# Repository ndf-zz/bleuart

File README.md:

# bleuart

ESP32 BLE to RS232 bridge

	BLE  <->  UART  <-- RX (RS232)
	                --> TX (RS232)

Using an ESP32-WROOM-32E module, BLEUART provides
a low-tech BLE to RS232 UART bridge. Data is transferred
via write and notify under a single custom GATT service
with ID 11e6b0a4-99c7-4647-956b-8a57cb5907d9.

Advertises device "location" (CNAME) via
manufacturer data. Initial bonding PIN is 0.

## Characteristics

UUID | Function | Type | Actions
--- | --- | --- | ---
0000b0a4-99c7-4647-956b-8a57cb5907d9 | Pin | uint32 (0-999999) | write
0001b0a4-99c7-4647-956b-8a57cb5907d9 | UART RX | bytes | notify
0010b0a4-99c7-4647-956b-8a57cb5907d9 | UART TX | bytes | write
0100b0a4-99c7-4647-956b-8a57cb5907d9 | CNAME "Location" | bytes | read/write
1000b0a4-99c7-4647-956b-8a57cb5907d9 | DNAME "Device Name" | bytes | write
f074b0a4-99c7-4647-956b-8a57cb5907d9 | FOTA | bytes | write
0x2a26 | Firmware Version | bytes | read

## Known Issues/Limitations

   - Secure boot V1 is used only as a fancy CRC for OTA updates.
     Todo: Move to V2.
   - Re-flashable bootloader needs to be booted once and then re-flashed
     to correct the re-flashable stage 2 digest. Todo: Move to V2 and or
     one-time flash.
   - LE security is circumvented through use of fixed pairing pin. Todo: OOB.
   - Private addrs do not yet work as expected. Todo: Investigate 
     implementation of RPA 0x2ac9.
   - RS232 line driver/receiver is always on, even when device cannot
     receive data due to light sleep. Todo: Use GPIO
     to switch power to line driver.
   - Test pads GPIO13/15 are inaccessible and floating. Todo:
     Add pull-ups and relocate pads with nearby ground pad for
     factory reset option.
   - Reflashable plain text bootloader assumed. Todo: Investigate
     encrypted flash, encrypted OTA transport.
   - App rollback not supported. Todo: Debug OTA partition
     errors in bootloader and check ota rollback tools.

## FOTA

Write SSID and PSK to GATT characteristic 0xf074 separated
by a null character. Eg:

	b'SSID\0wpapskstr'

Device will connect to nominated ssid, fetch firmware 
then reboot. Base URL for update is set in menuconfig
options. In case of error or timeout, device will reboot to
previous firmware.

Update file requested:

	11e6b0a4-99c7-4647-956b-8a57cb5907d9.bin

## Build & Flash

   - Install ESP-IDF & run export
   - Set target
   - Create secure boot signing key if required
   - Run burnin.sh, reboot board and then run reburn.sh

	$ . ../esp-idf/export.sh
	$ idf.py set-target esp32
	$ idf.py secure-generate-signing-key secure_boot_signing_key.pem
	$ ./burnin.sh
	$ ./reburn.sh

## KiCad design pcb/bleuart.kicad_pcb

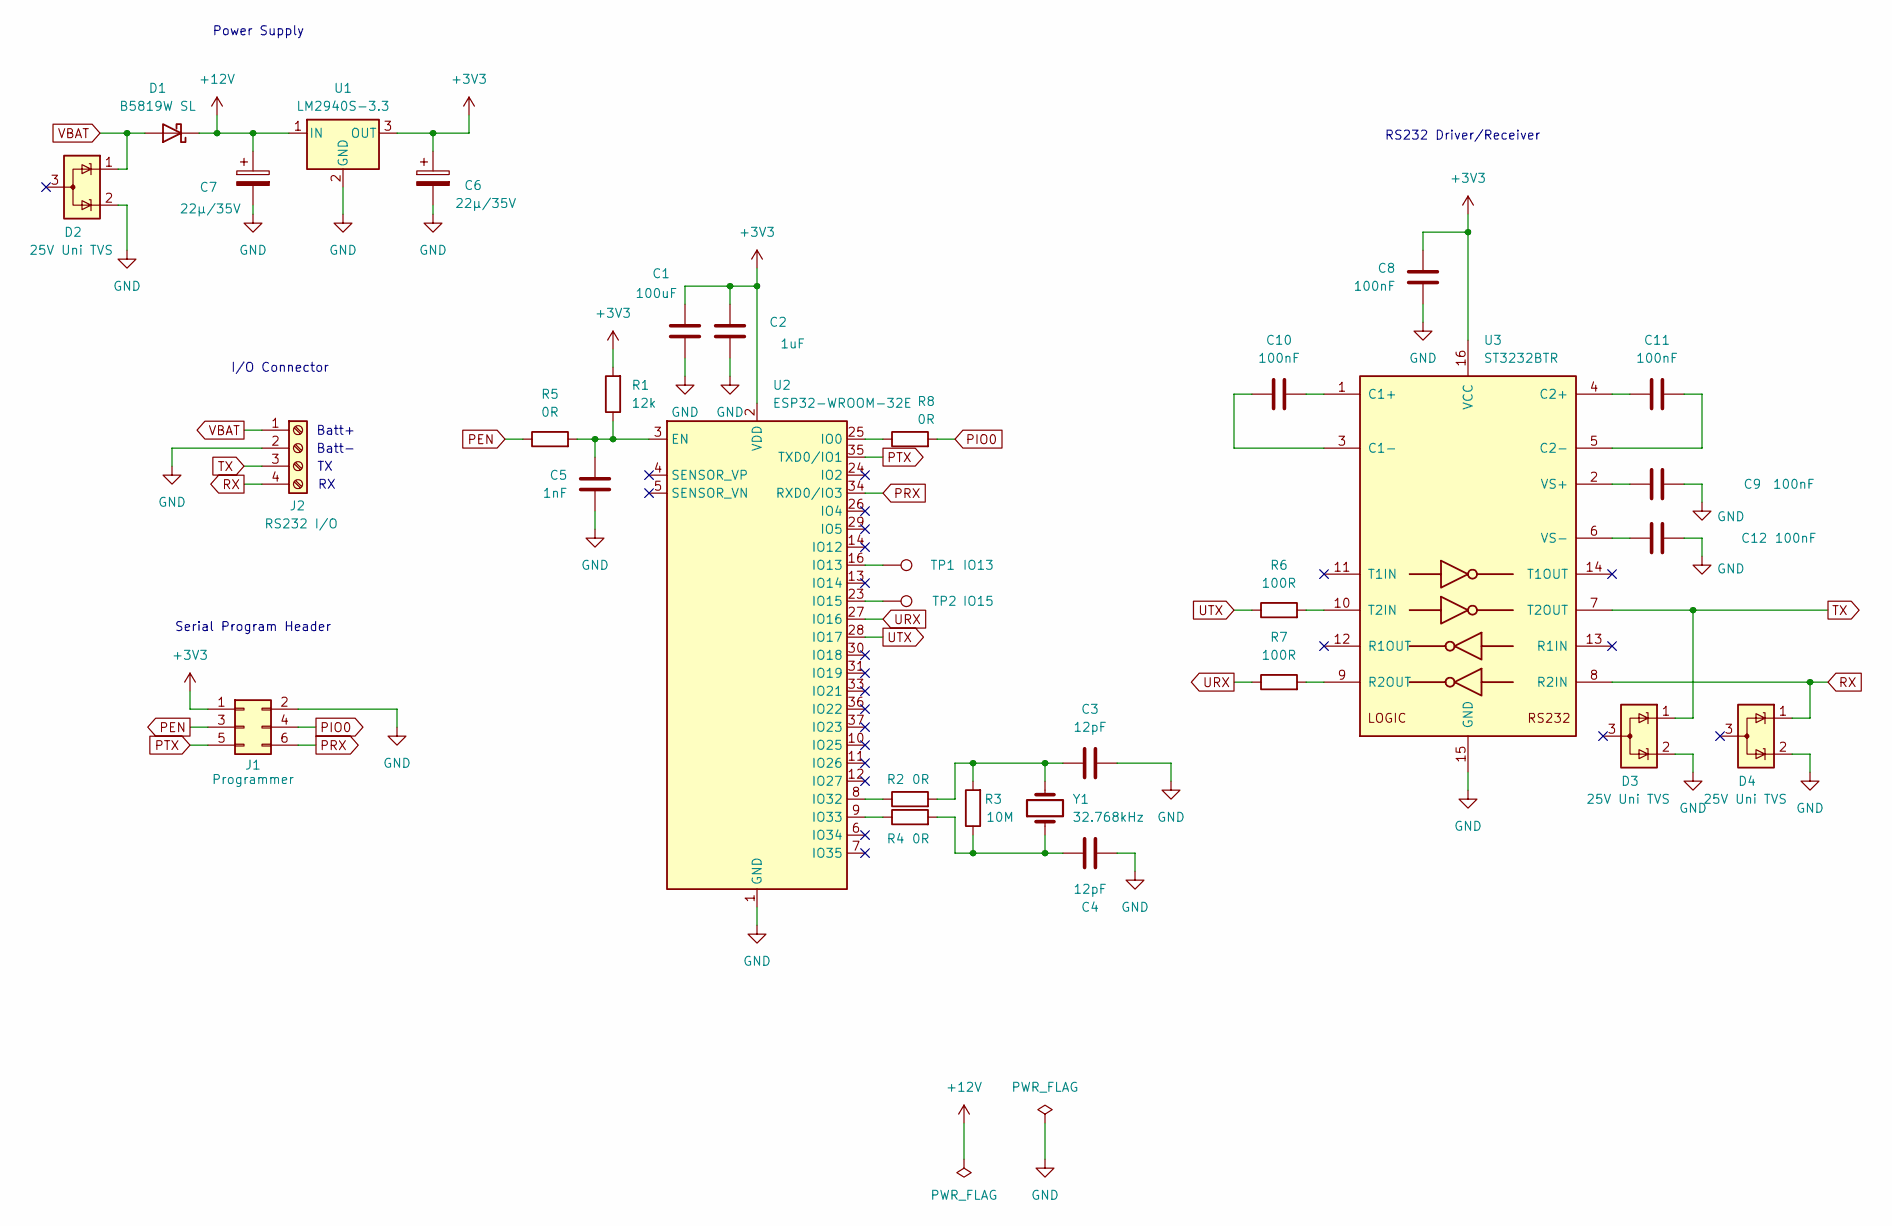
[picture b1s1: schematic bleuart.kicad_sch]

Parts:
C1: 100uF; C_1206_3216Metric; LCSC C15008
C2: 1uF; C_0603_1608Metric; LCSC C15849
C3, C4: 12pF; C_0603_1608Metric; LCSC C1642
C5: 1nF; C_0603_1608Metric; LCSC C1588
C6, C7: 22µ/35V; CP_Elec_5x5.8; LCSC C494835
C8, C9, C10, C11, C12: 100nF; C_0603_1608Metric; LCSC C14663
D1: B5819W SL; D_SOD-123; LCSC C8598
D2, D3, D4: 25V Uni TVS; SOT-23; LCSC C95343
J1: Programmer; PinHeader_2x03_P2.54mm_Vertical
J2: RS232 I/O; TerminalBlock_Phoenix_PT-1,5-4-5.0-H_1x04_P5.00mm_Horizontal
R1: 12k; R_0603_1608Metric; LCSC C22790
R2, R4, R5, R8: 0R; R_0603_1608Metric; LCSC C95177
R3: 10M; R_0603_1608Metric; LCSC C7250
R6, R7: 100R; R_0603_1608Metric; LCSC C22775
TP1: IO13; TestPoint_Pad_D1.5mm
TP2: IO15; TestPoint_Pad_D1.5mm
U1: LM2940S-3.3; SOT-223-3_TabPin2; LCSC C596335
U2: ESP32-WROOM-32E; LCSC C3013935
U3: ST3232BTR; TSSOP-16_4.4x5mm_P0.65mm; LCSC C118284
Y1: 32.768kHz; Crystal_SMD_MicroCrystal_CC7V-T1A-2Pin_3.2x1.5mm; LCSC C32346

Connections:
+3V3: C1.1, C2.1, C6.1, C8.1, J1.1, R1.2, U1.3 (OUT), U2.2 (VDD), U3.16 (VCC)
+12V: C7.1, D1.1 (K), U1.1 (IN)
GND: C1.2, C2.2, C3.2, C4.2, C5.2, C6.2, C7.2, C8.2, C9.2, C12.2, D2.2 (K), D3.2 (K), D4.2 (K), J1.2, J2.2, U1.2 (GND), U2.1 (GND), U2.15 (GND), U2.38 (GND), U2.39 (GND), U3.15 (GND)
unnamed: C3.1, R2.2, R3.2, Y1.2
unnamed: C4.1, R3.1, R4.2, Y1.1
unnamed: C5.1, R1.1, R5.2, U2.3 (EN)
unnamed: R8.1, U2.25 (IO0)
unnamed: TP1.1, U2.16 (IO13)
unnamed: TP2.1, U2.23 (IO15)
unnamed: R2.1, U2.8 (IO32)
unnamed: R4.1, U2.9 (IO33)
unnamed: C10.2, U3.1 (C1+)
unnamed: C10.1, U3.3 (C1-)
unnamed: C11.1, U3.4 (C2+)
unnamed: C11.2, U3.5 (C2-)
unnamed: R7.2, U3.9 (R2OUT)
unnamed: R6.2, U3.10 (T2IN)
unnamed: C9.1, U3.2 (VS+)
unnamed: C12.1, U3.6 (VS-)
PEN: J1.3, R5.1
PIO0: J1.4, R8.2
PRX: J1.6, U2.34 (RXD0/IO3)
PTX: J1.5, U2.35 (TXD0/IO1)
RX: D4.1 (K), J2.4, U3.8 (R2IN)
TX: D3.1 (K), J2.3, U3.7 (T2OUT)
URX: R7.1, U2.27 (IO16)
UTX: R6.1, U2.28 (IO17)
VBAT: D1.2 (A), D2.1 (K), J2.1

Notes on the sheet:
Batt+
RS232 Driver/Receiver
Power Supply
Batt-
I/O Connector
Serial Program Header

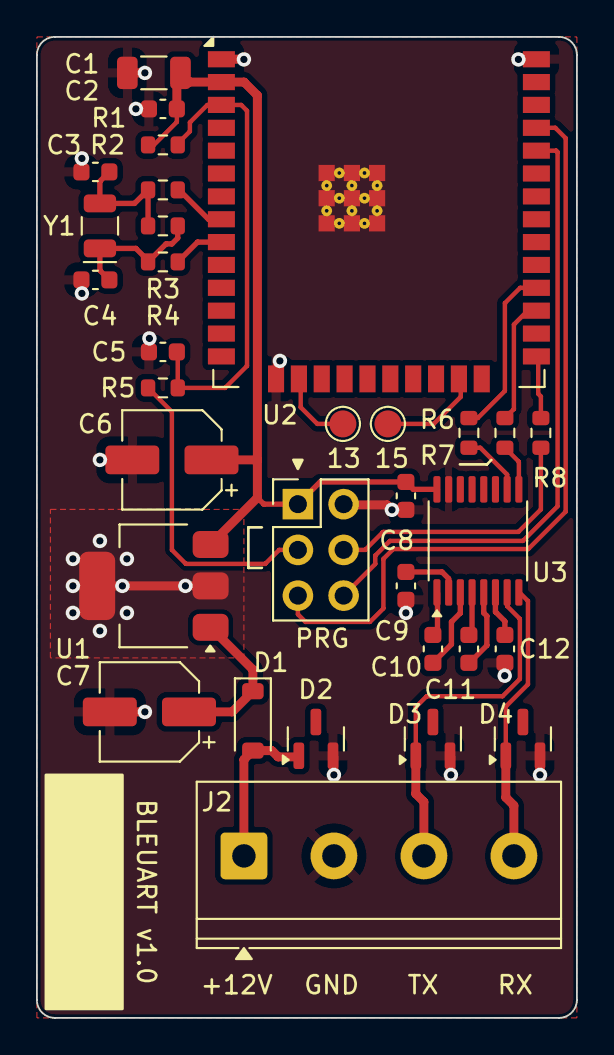
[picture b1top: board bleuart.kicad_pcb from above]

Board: 2 copper layers, 30.0 x 54.5 mm, 32 parts (0 on the bottom side), 28 nets.

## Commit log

2025-09-04 Version 1.0.0
2025-09-04 fix path typo in reburn script
2025-09-07 Drop read flag on RX and notify via mbuf instead of global rx
2025-09-07 Add example client config script
2025-09-09 Add OTA trigger to config script
2025-09-09 Adjust connection parameters to reduce disconnects with bluez/bleak
2025-10-04 Edit DNAME from config script
